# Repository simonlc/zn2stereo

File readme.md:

# Capcom ZN-2 stereo breakout board

The ZN-2 stereo breakout board is a custom PCB that connects to a ZN-2 audio header and provide line level stereo output. The attenuation circuit is based on the Sanwa VC-J [documented here](http://www.neo-geo.com/forums/showthread.php?172861-A-different-attenuation-circuit).

It's mounted by a single standoff, and is supported by the connector that sits on the stereo header.

- Online BOM: https://octopart.com/bom-tool/YipwlKb2
- Purchase bare PCB online: https://oshpark.com/shared_projects/Dj41HkF0

### Donate: https://paypal.me/zn2stereo

## Assembly

To assemble the board, soldering experience is needed. Parts in the BOM must be acquired, and a custom PCB printed. The PCB can be printed from anywhere, but a link is provided to purchase from OSH Park for convenience. If you have any questions regarding the installation or purchase please create an issue.

## Installation

For ZN-2 games, the stereo/mono switch next to the volume pot must be set to stereo. The game also needs to be set to stereo in the test menu.

The BOM includes M3 standoff and screws. Depending on your PCB standoffs, these might not be the right size, please double check!

## Compatibility

This board may be compatible with other ZN-2 style hardware.

| Hardware           | Compatibility |
| ------------------ | ------------- |
| Capcom ZN-2        | ✅  Working    |
| Capcom ZN-1        | ✅  Working    |
| Taito G-Net        | ❓  Not tested |
| Tecmo TPS          | ❓  Not tested |
| Taito FX-1A System | ❓  Not tested |
| Taito FX-1B System | ❓  Not tested |

## License
Licensed under the TAPR Open Hardware License (www.tapr.org/OHL)

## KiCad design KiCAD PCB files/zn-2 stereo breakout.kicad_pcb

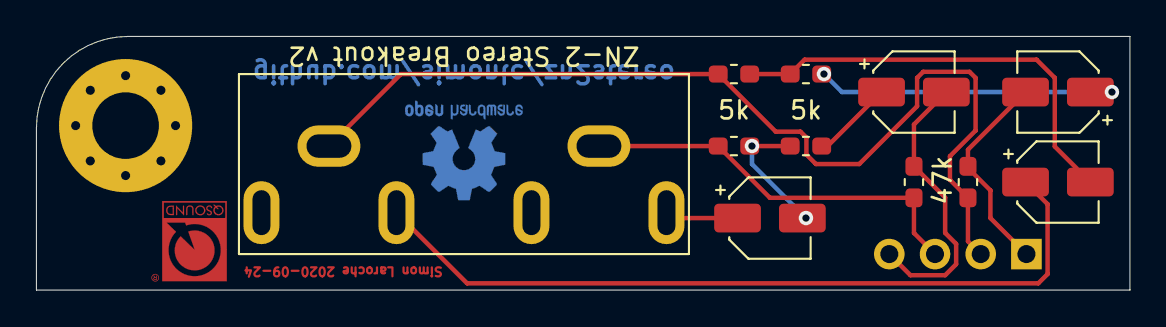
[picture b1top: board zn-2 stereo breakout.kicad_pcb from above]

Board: 2 copper layers, 60.8 x 14.1 mm, 12 parts (1 on the bottom side), 10 nets.

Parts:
C5, C6, C7, C8: 10u; CP_Elec_4x5.8
J1: Dual_AudioJack1_Ground_Switch; Switchcraft PJRAN2X1U01AUX
J5: Conn_01x04_Male; PinSocket_1x04_P2.54mm_Vertical
R3, R4: 10k; R_0603_1608Metric_Pad1.05x0.95mm_HandSolder
R5, R6: 5k; R_0603_1608Metric_Pad1.05x0.95mm_HandSolder
R7, R8: 47k; R_0603_1608Metric_Pad1.05x0.95mm_HandSolder

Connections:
/L+OUT: C5.1, J1.L+
/L-OUT: J1.L-, J5.2, R3.1, R7.1
/LEFT+: C7.2, J5.1, R7.2
/R+OUT: C6.1, J1.R+
/R-OUT: J1.R-, J5.3, R5.1, R8.1
/RIGHT+: C8.2, J5.4, R8.2
unnamed: C5.2, R3.2, R4.1
unnamed: C6.2, R5.2, R6.1
unnamed: C7.1, R4.2
unnamed: C8.1, R6.2

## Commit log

2020-09-25 Update readme with images
2020-09-25 Fix link syntax
2020-09-25 Readme formating
2020-09-25 Add section on assembly
2020-09-25 Move bom file
2020-09-25 Update BOM and add section in readme about standoffs
